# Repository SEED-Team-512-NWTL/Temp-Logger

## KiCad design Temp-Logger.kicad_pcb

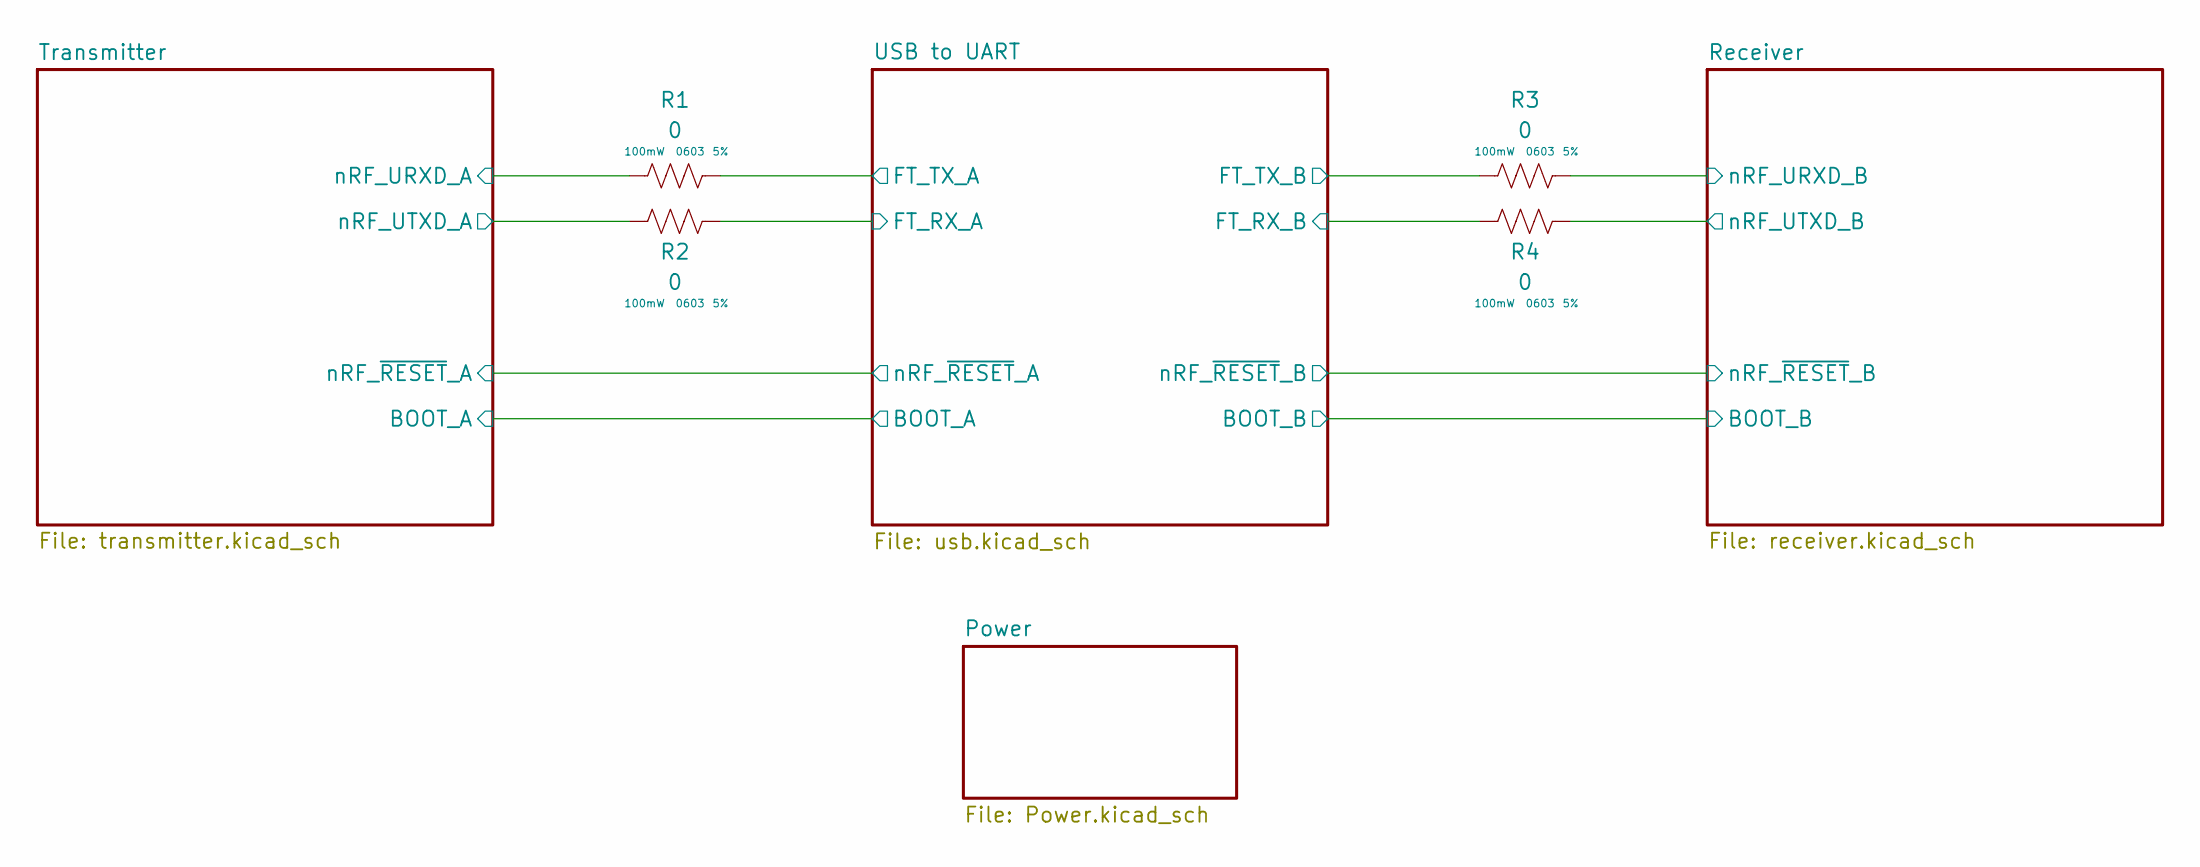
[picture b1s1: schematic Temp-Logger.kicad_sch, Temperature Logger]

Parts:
R1, R2, R3, R4: 0; R_0603_1608Metric_Pad0.98x0.95mm_HandSolder; Tolerance 5%; LCSC C177335

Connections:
/Receiver/nRF_URXD_B: R3.2; also elsewhere on the board
/Receiver/nRF_UTXD_B: R4.2; also elsewhere on the board
/Transmitter/nRF_URXD_A: R1.1; also elsewhere on the board
/Transmitter/nRF_UTXD_A: R2.1; also elsewhere on the board
/USB to UART/FT_RX_A: R2.2; also elsewhere on the board
/USB to UART/FT_RX_B: R4.1; also elsewhere on the board
/USB to UART/FT_TX_A: R1.2; also elsewhere on the board
/USB to UART/FT_TX_B: R3.1; also elsewhere on the board

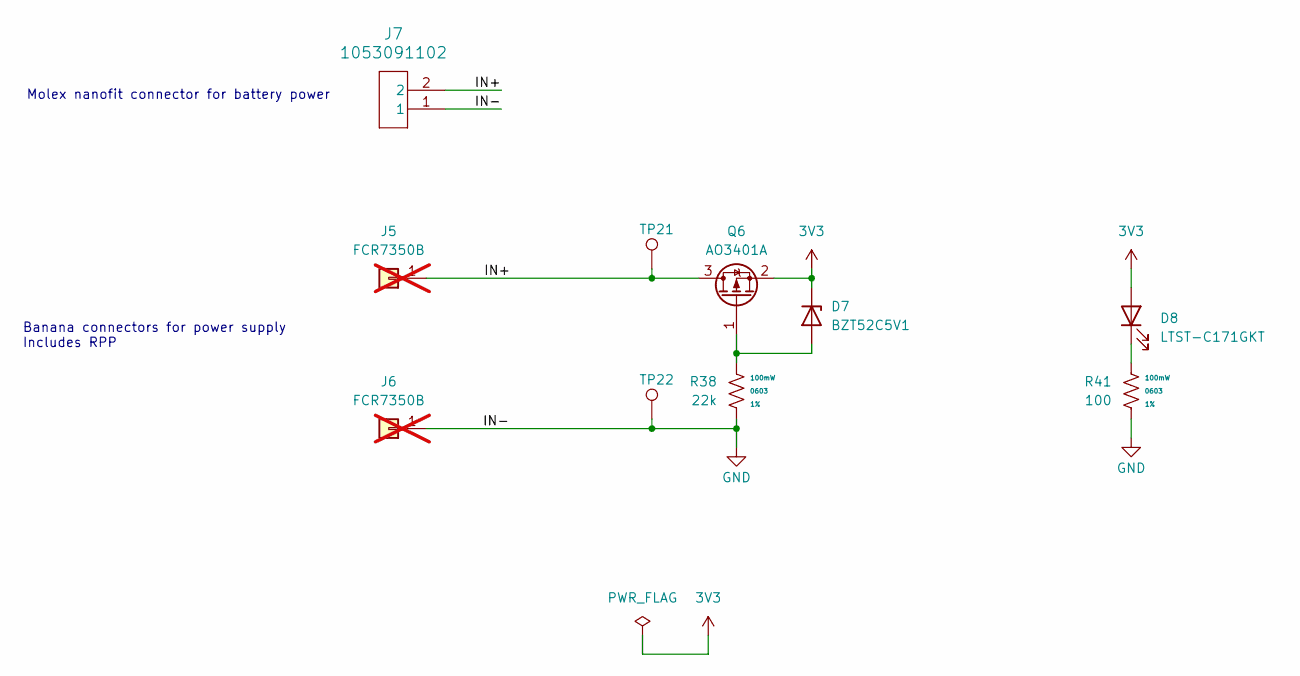
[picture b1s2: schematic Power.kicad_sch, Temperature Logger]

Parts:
D7: BZT52C5V1; D_SOD-123; LCSC C2117
D8: LTST-C171GKT; LED_0805_2012Metric; LCSC C913075
J5, J6: FCR7350B; Banana_Cliff_FCR7350B_S16N-PC_Horizontal; not fitted
J7: 1053091102; LCSC C2938824
Q6: AO3401A; SOT-23; LCSC C15127
R38: 22k; R_0603_1608Metric_Pad0.98x0.95mm_HandSolder; Tolerance 1%; LCSC C114065
R41: 100; R_0603_1608Metric_Pad0.98x0.95mm_HandSolder; Tolerance 1%; LCSC C105588
TP21, TP22: 1.0mm; TestPoint_Pad_D1.0mm

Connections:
3V3: D7.1 (K), D8.2 (A), Q6.2 (S); also elsewhere on the board
/Power/IN+: J5.1 (Pin_1_1), J7.2, Q6.3 (D), TP21.1 (1_1)
GND: J6.1 (Pin_1_1), J7.1, R38.1, R41.1, TP22.1 (1_1); also elsewhere on the board
unnamed: D7.2 (A), Q6.1 (G), R38.2
unnamed: D8.1 (K), R41.2

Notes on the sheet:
Banana connectors for power supply Includes RPP
Molex nanofit connector for battery power

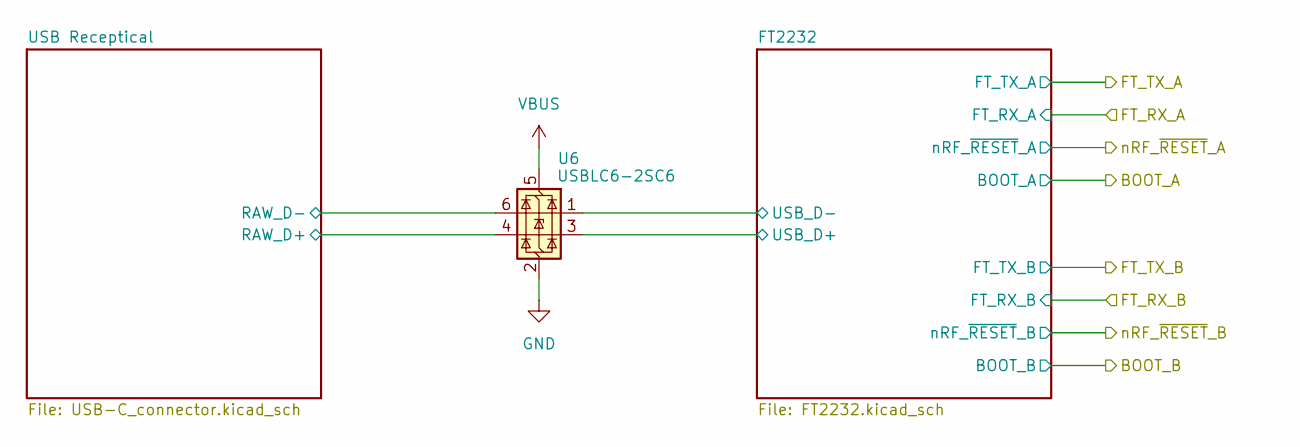
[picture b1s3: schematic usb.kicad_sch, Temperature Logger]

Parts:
U6: USBLC6-2SC6; SOT-23-6; LCSC C7519

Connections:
/USB to UART/FT2232/USB_D+: U6.3 (I/O2); also elsewhere on the board
/USB to UART/FT2232/USB_D-: U6.1 (I/O1); also elsewhere on the board
/USB to UART/USB Receptical/RAW_D+: U6.4 (I/O2); also elsewhere on the board
/USB to UART/USB Receptical/RAW_D-: U6.6 (I/O1); also elsewhere on the board
GND: U6.2 (GND); also elsewhere on the board
VBUS: U6.5 (VBUS); also elsewhere on the board

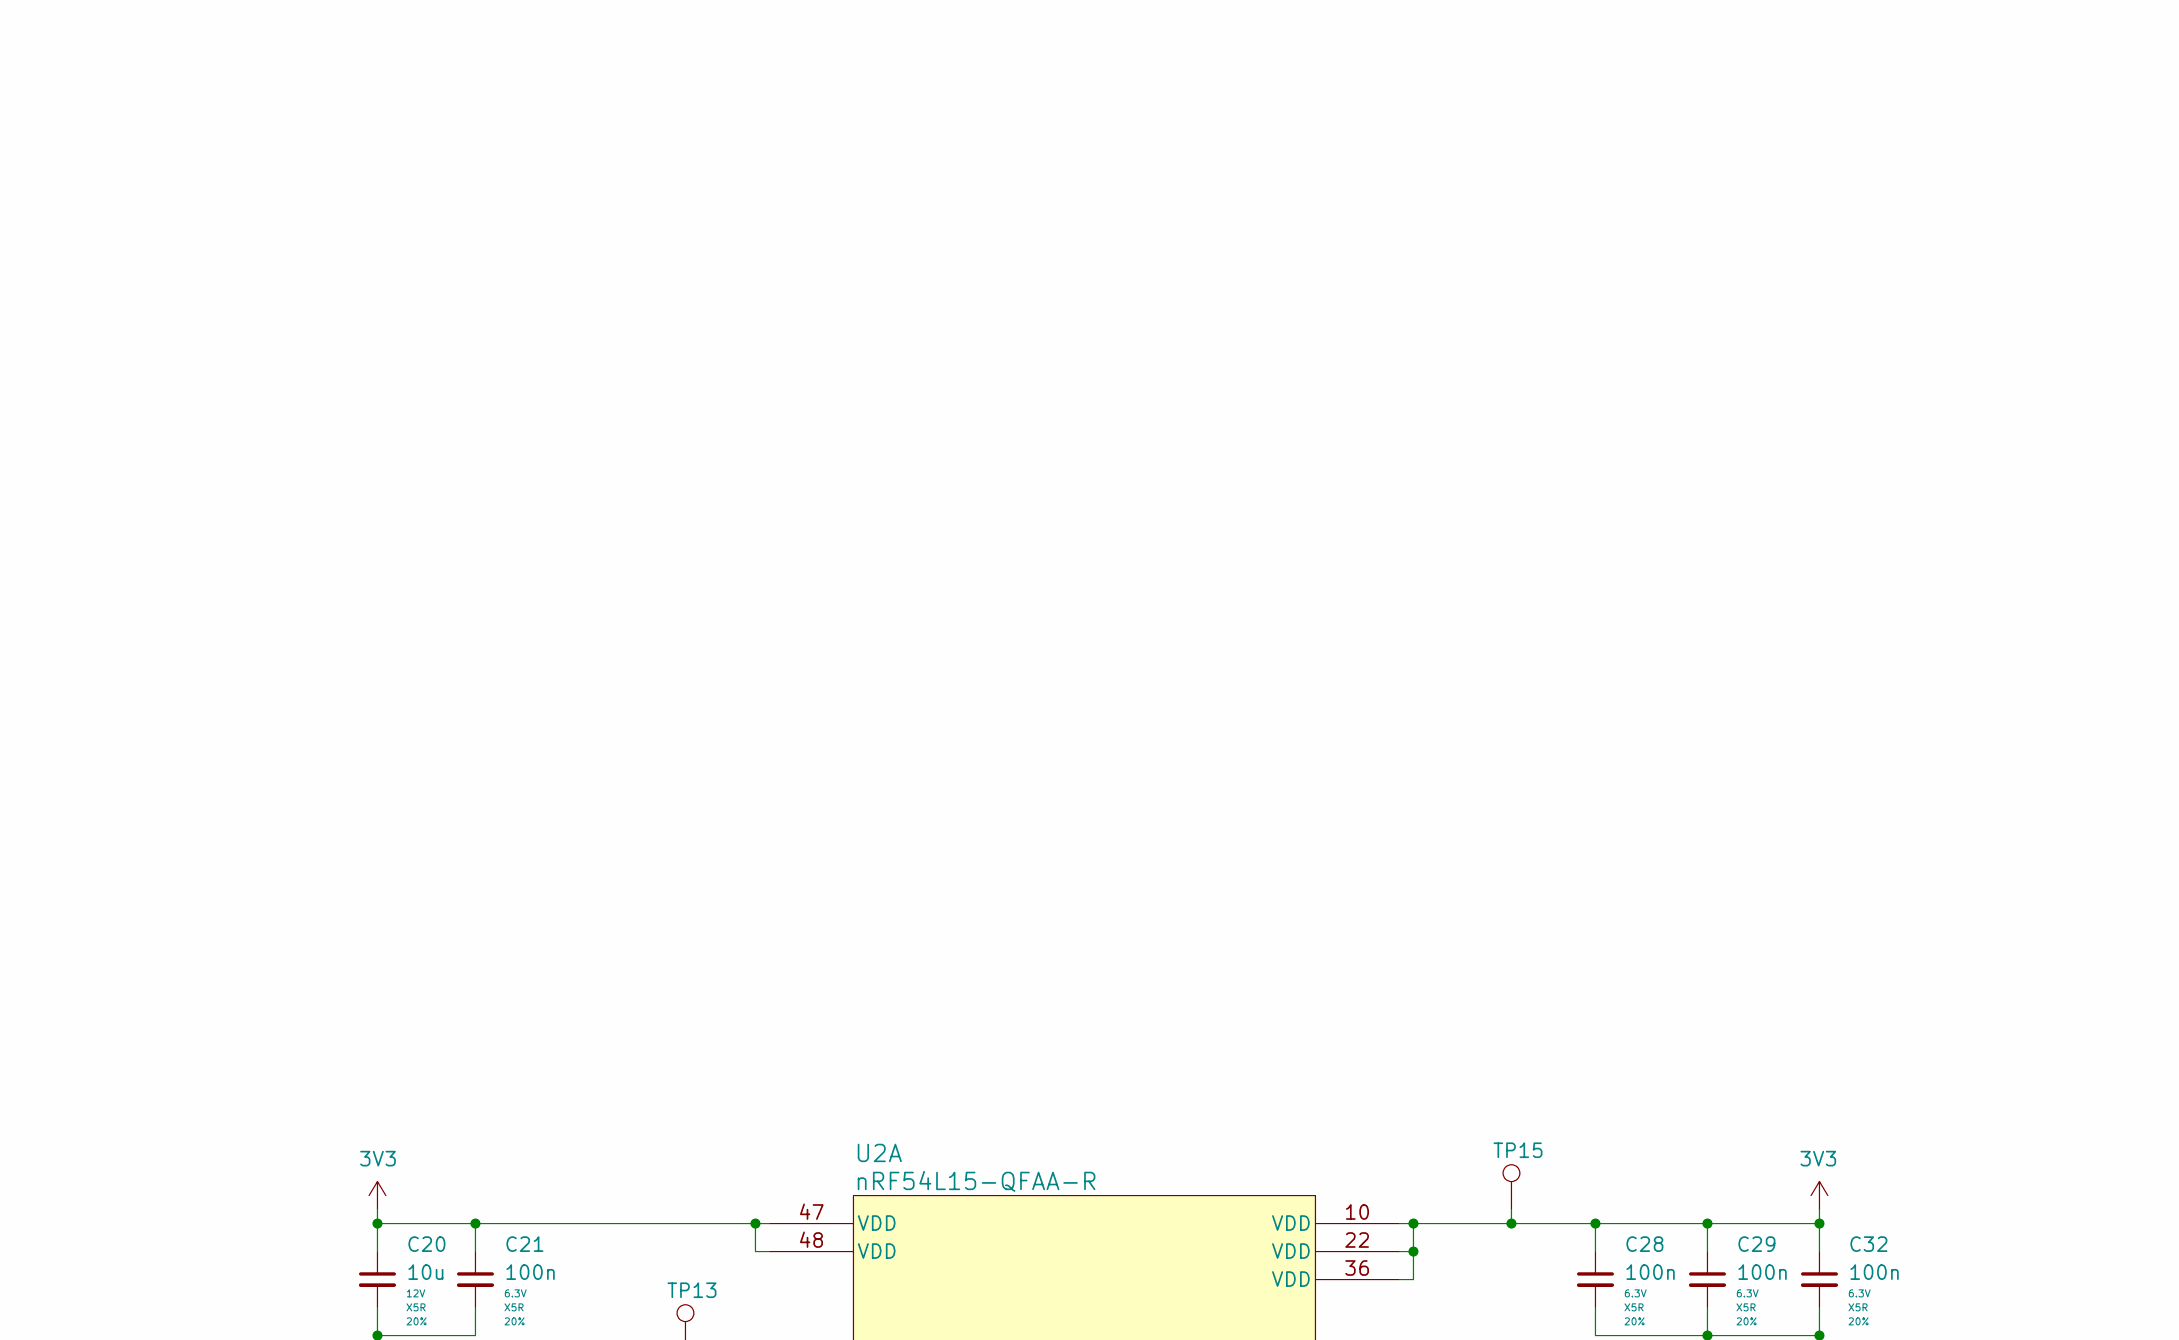
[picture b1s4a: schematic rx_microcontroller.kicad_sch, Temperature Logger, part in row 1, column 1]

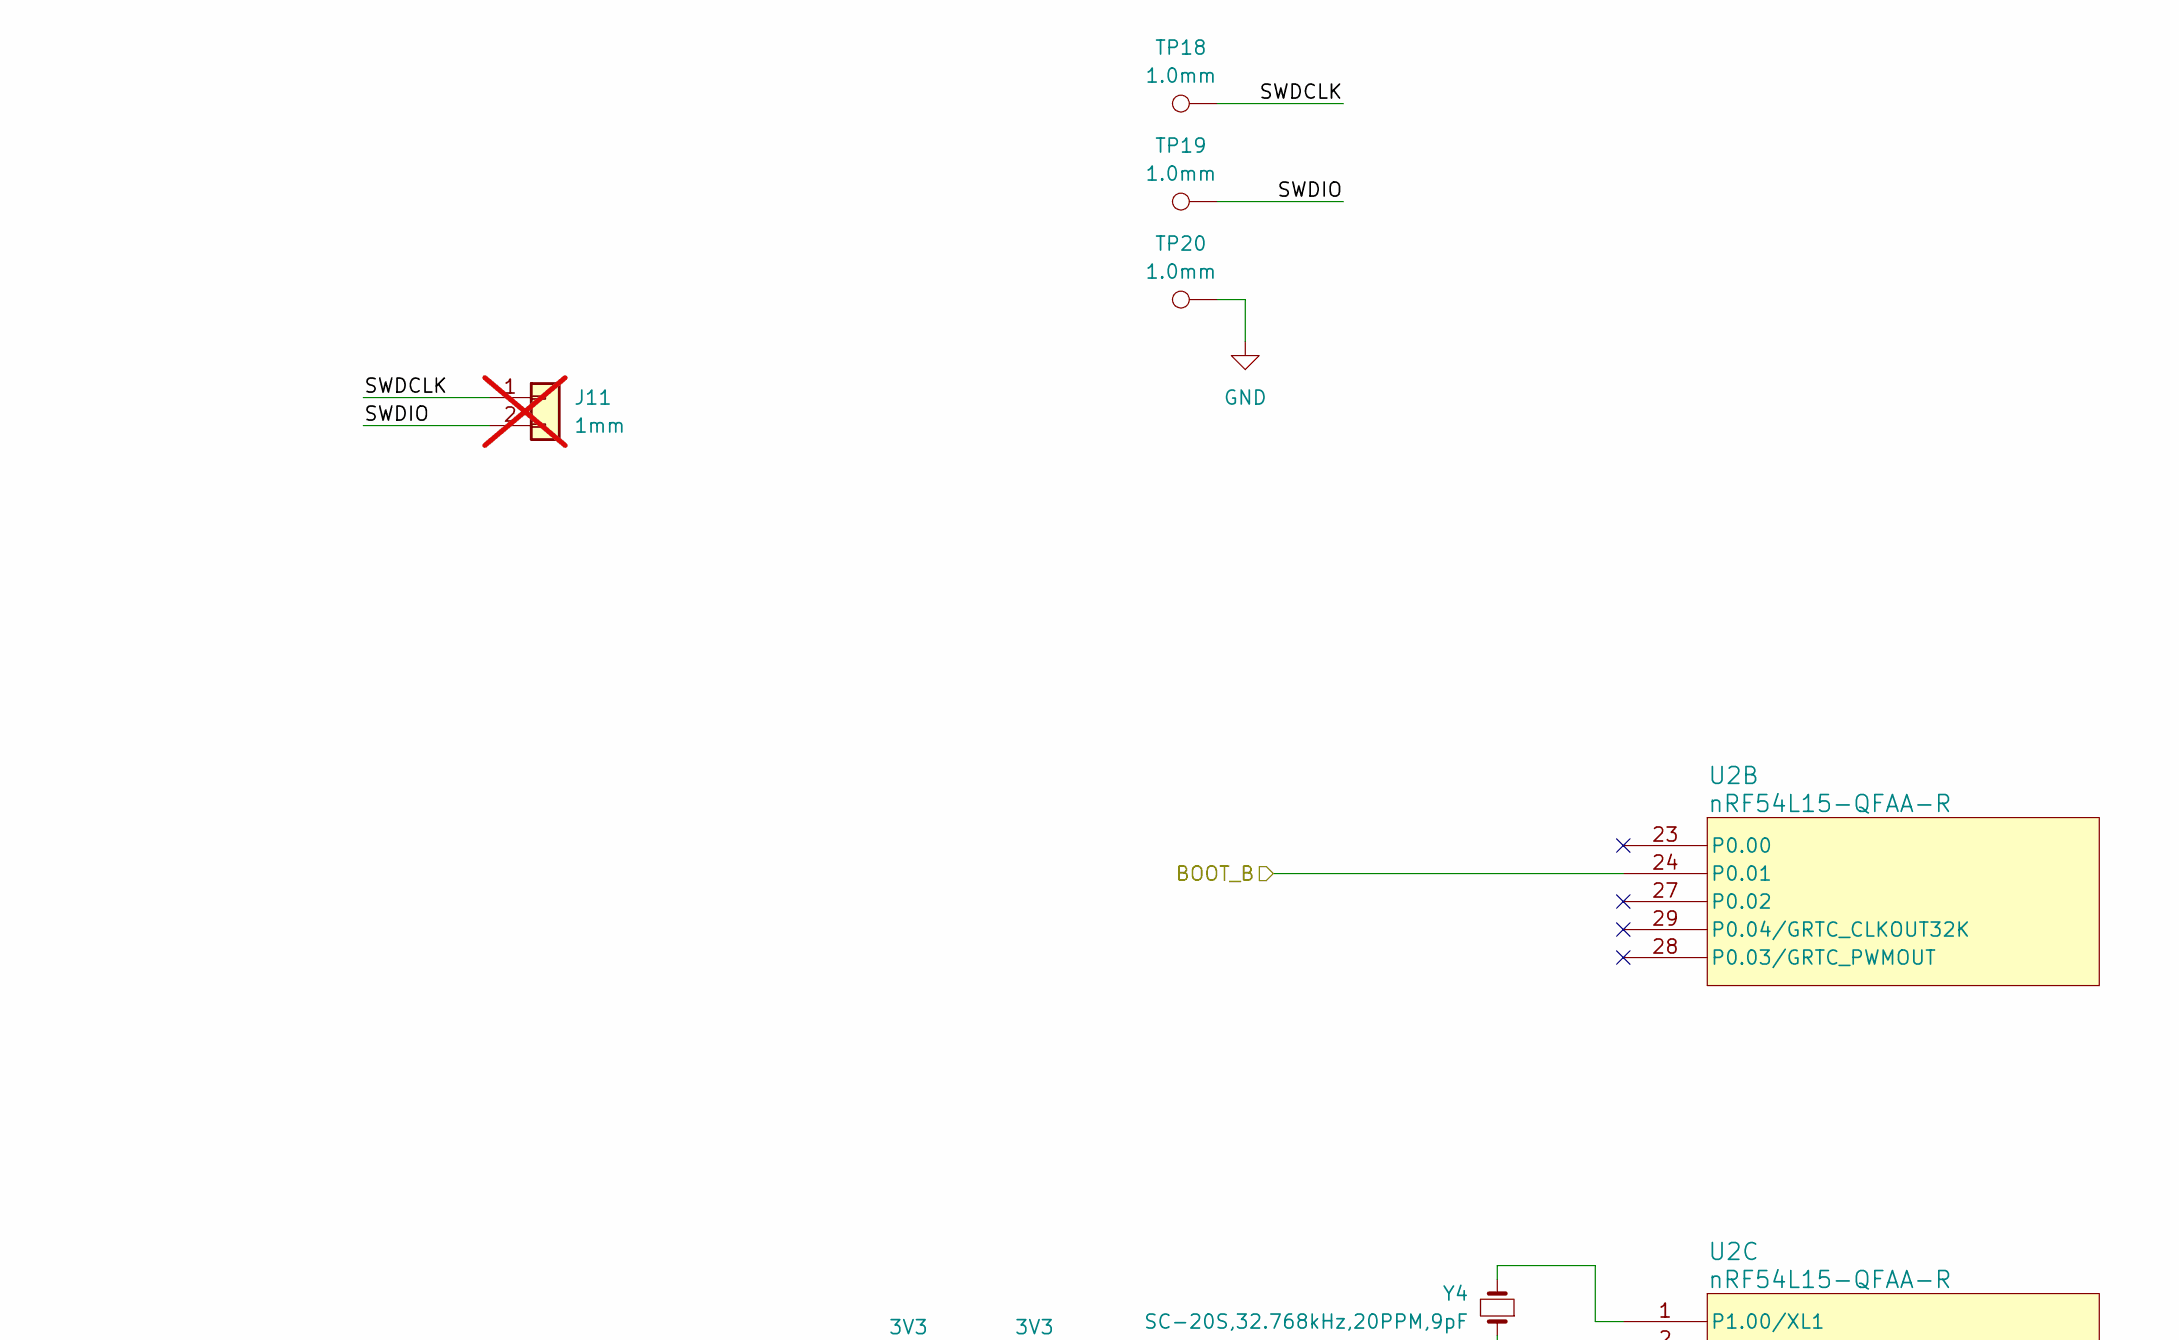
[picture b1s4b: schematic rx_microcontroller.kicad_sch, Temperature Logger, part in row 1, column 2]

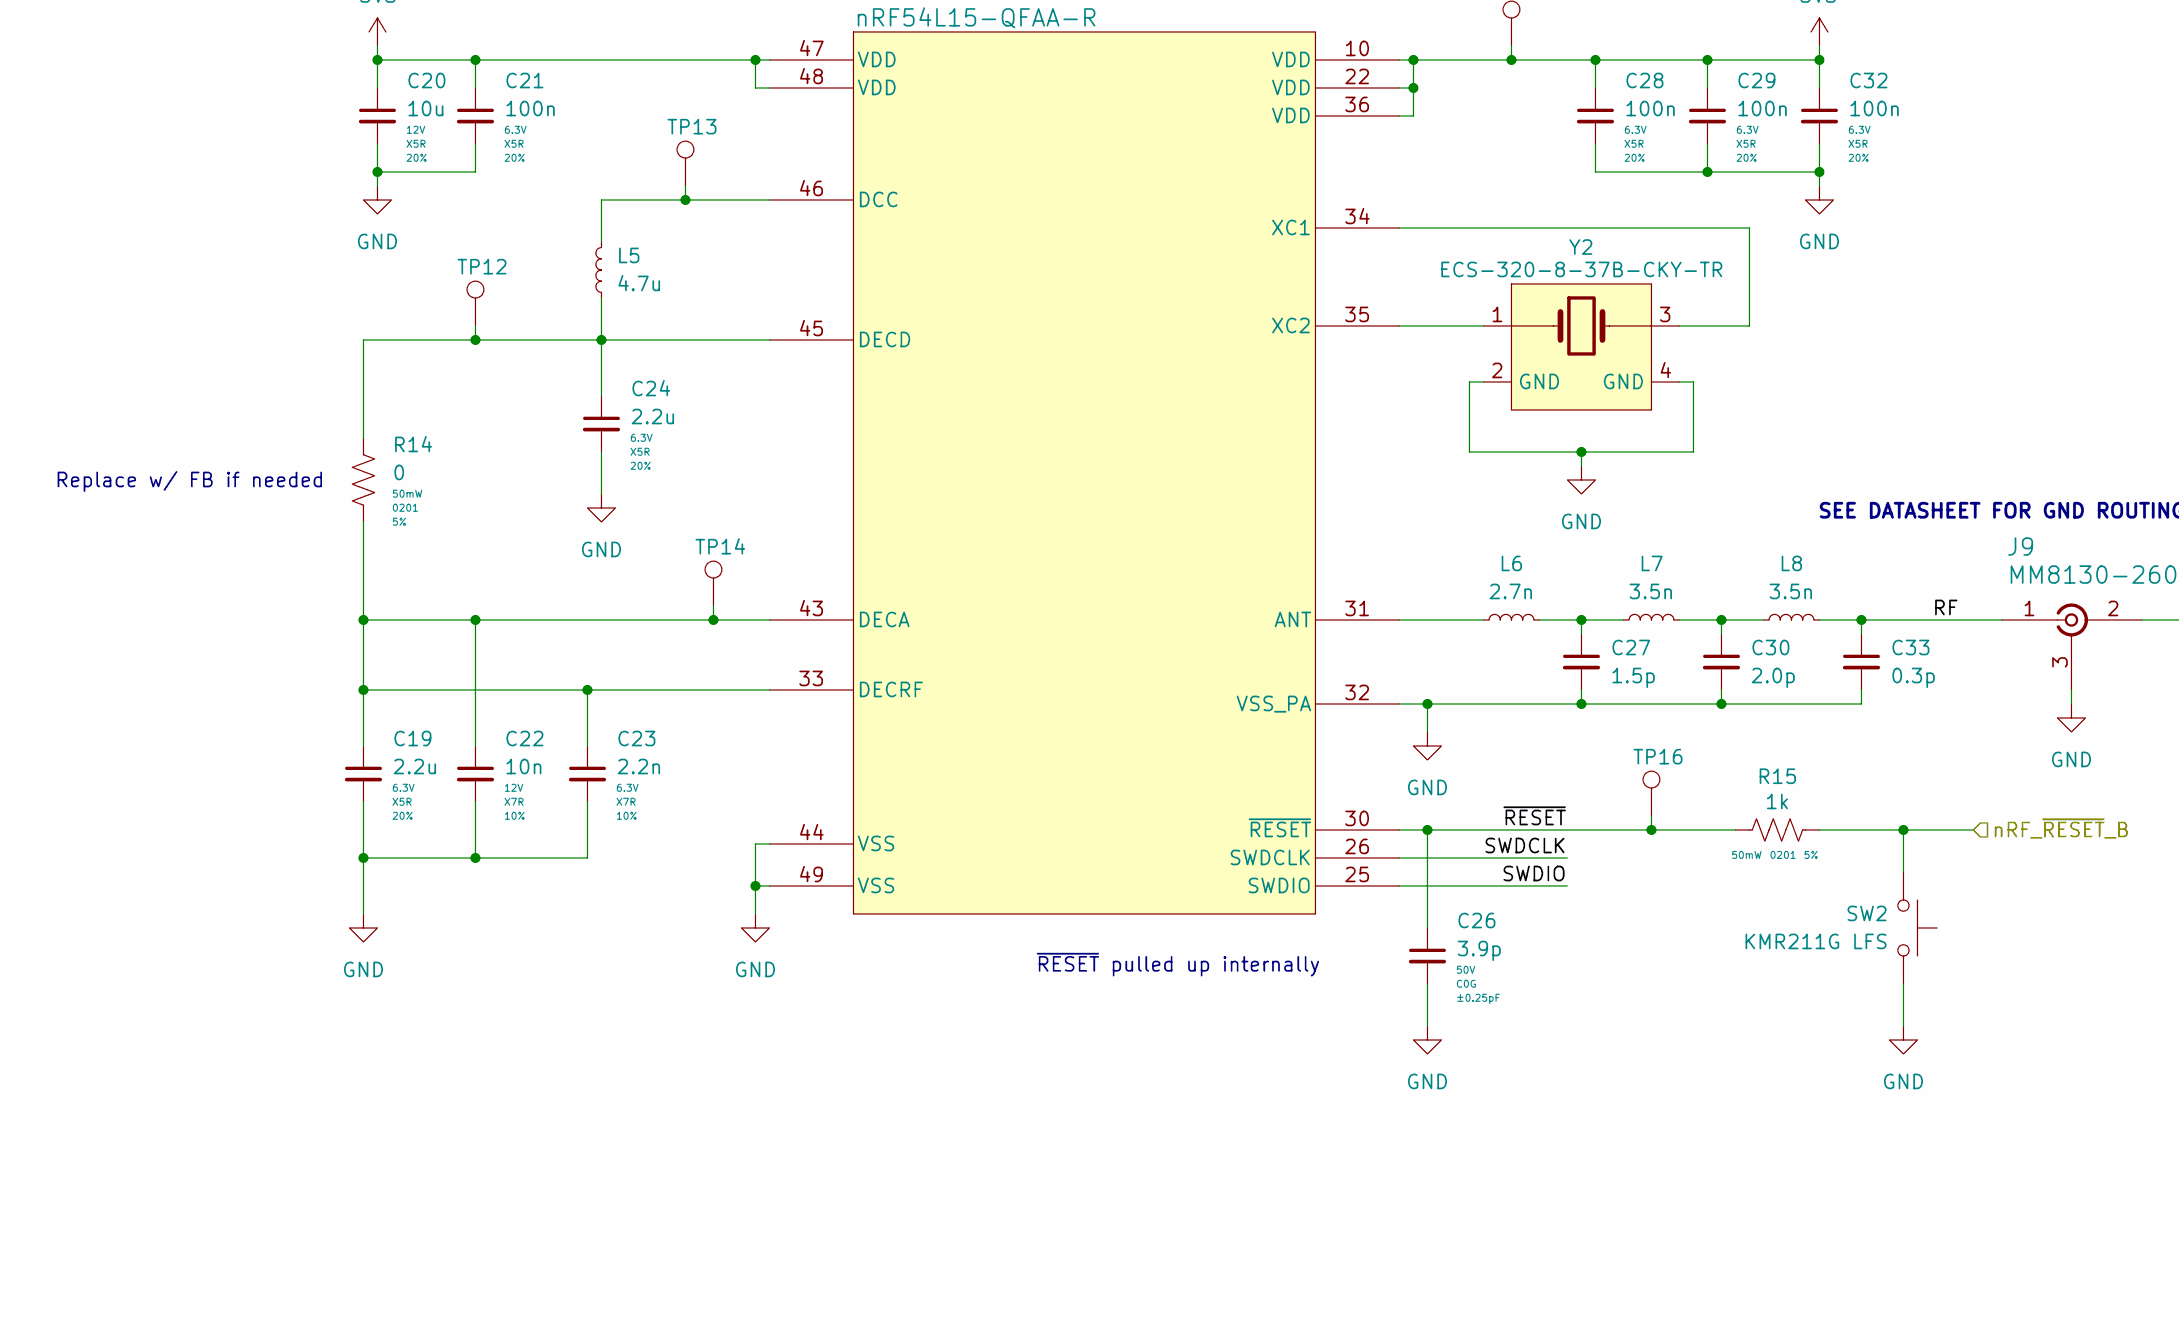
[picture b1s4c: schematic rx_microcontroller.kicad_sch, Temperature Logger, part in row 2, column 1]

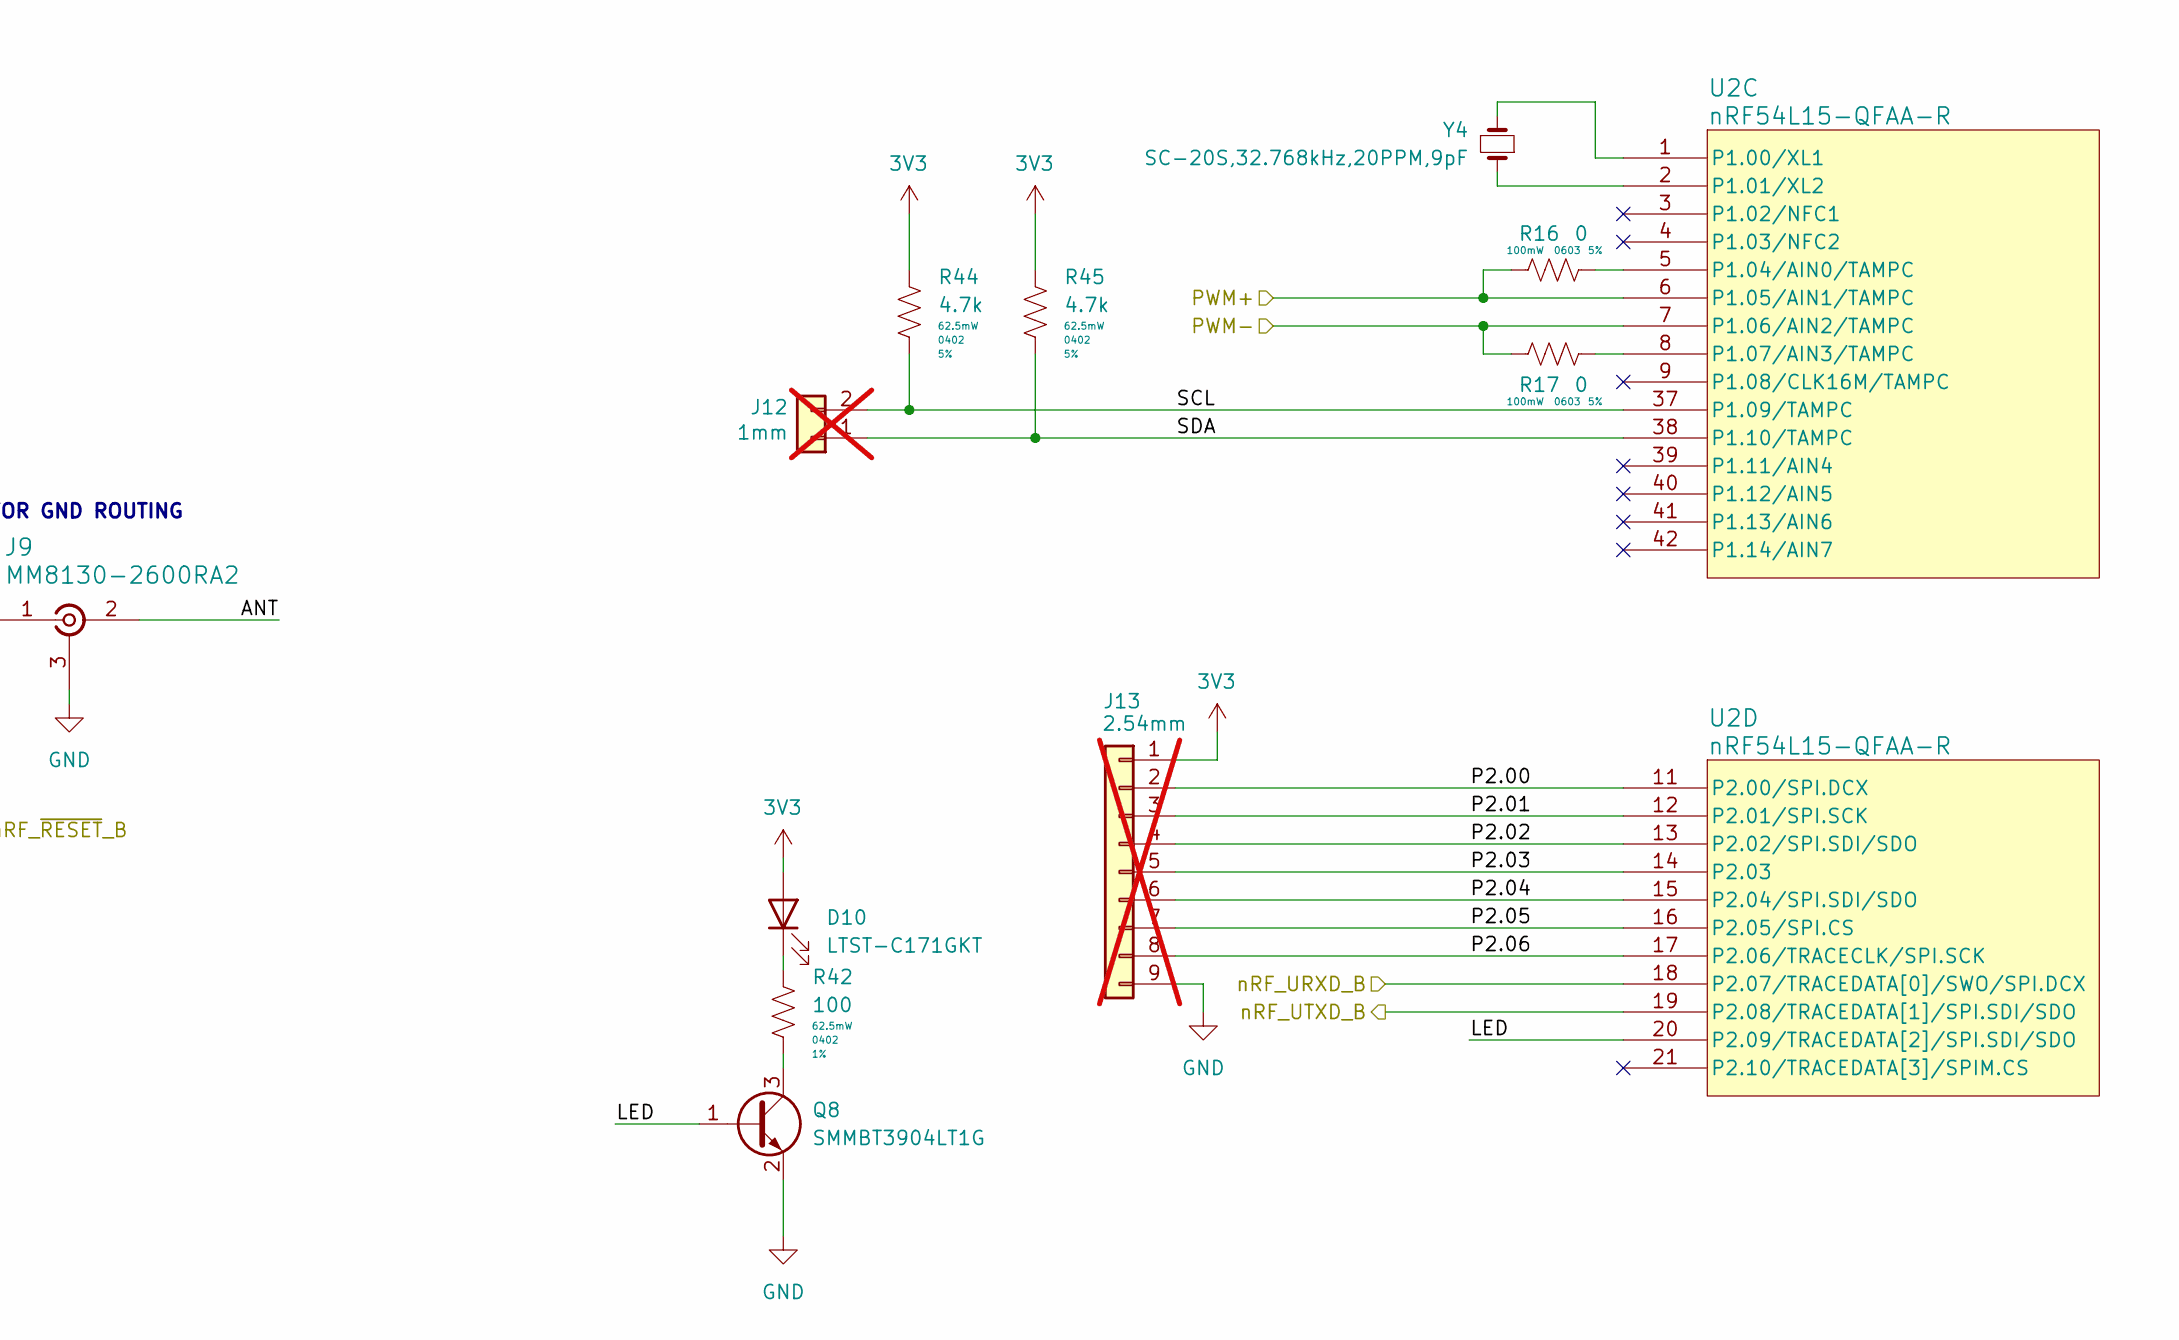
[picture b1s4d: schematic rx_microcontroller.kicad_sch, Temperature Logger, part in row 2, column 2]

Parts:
C19, C24: 2.2u; C_0201_0603Metric; Voltage Rating 6.3V; Tolerance 20%; LCSC C76933
C20: 10u; C_0402_1005Metric_Pad0.74x0.62mm_HandSolder; Voltage Rating 12V; Tolerance 20%; LCSC C15525
C21, C28, C29, C32: 100n; C_0201_0603Metric; Voltage Rating 6.3V; Tolerance 20%; LCSC C284992
C22: 10n; C_0201_0603Metric; Voltage Rating 12V; Tolerance 10%; LCSC C309453
C23: 2.2n; C_0201_0603Metric; Voltage Rating 6.3V; Tolerance 10%; LCSC C526947
C26: 3.9p; C_0201_0603Metric; Voltage Rating 50V; Tolerance ±0.25pF; LCSC C76926
C27: 1.5p; C_0201_0603Metric; Part Number GJM0335C1E1R5WB01; LCSC C435397
C30: 2.0p; C_0201_0603Metric; Part Number GJM0335C1E2R0WB01; LCSC C668326
C33: 0.3p; C_0201_0603Metric; LCSC C76927
D10: LTST-C171GKT; LED_0805_2012Metric; LCSC C913075
J9: MM8130-2600RA2; LCSC C167503
J11, J12: 1mm; PinHeader_1x02_P1.00mm_Vertical; not fitted
J13: 2.54mm; PinHeader_1x09_P2.54mm_Vertical; not fitted
L5: 4.7u; L_0603_1608Metric; LCSC C76799
L6: 2.7n; L_0201_0603Metric; Part Number GJM0335C1E1R5WB01; LCSC C7216765
L7, L8: 3.5n; L_0201_0603Metric; Part Number LQP03HQ3N5B02; LCSC C3911055
Q8: SMMBT3904LT1G; LCSC C84555
R14: 0; R_0201_0603Metric; Tolerance 5%; LCSC C100147
R15: 1k; R_0201_0603Metric; Tolerance 5%; LCSC C131396
R16, R17: 0; R_0603_1608Metric_Pad0.98x0.95mm_HandSolder; Tolerance 5%; LCSC C177335
R42: 100; R_0402_1005Metric_Pad0.72x0.64mm_HandSolder; Tolerance 1%; LCSC C82865
R44, R45: 4.7k; R_0402_1005Metric_Pad0.72x0.64mm_HandSolder; Tolerance 5%; LCSC C105870
SW2: KMR211G LFS; SW_Push_1P1T_NO_CK_KMR2; LCSC C221675
TP12, TP13, TP14, TP15, TP16, TP18, TP19, TP20: 1.0mm; TestPoint_Pad_D1.0mm
U2: nRF54L15-QFAA-R; NRF54L15-QFAA-R
Y2: ECS-320-8-37B-CKY-TR; LCSC C2636238
Y4: SC-20S,32.768kHz,20PPM,9pF; LCSC C97603

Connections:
3V3: C20.1, C21.1, C28.1, C29.1, C32.1, D10.2 (A), J13.1, R44.1, R45.1, TP15.1 (1_1), U2.10 (VDD), U2.22 (VDD), U2.36 (VDD), U2.47 (VDD), U2.48 (VDD); also elsewhere on the board
/Receiver/BOOT_B: U2.24 (P0.01); also elsewhere on the board
/Receiver/Piezoelectric/PWM+: R16.1, U2.6 (P1.05/AIN1/TAMPC); also elsewhere on the board
/Receiver/Piezoelectric/PWM-: R17.1, U2.7 (P1.06/AIN2/TAMPC); also elsewhere on the board
/Receiver/RX Microcontroller/ANT: J9.2 (OUT)
/Receiver/RX Microcontroller/LED: Q8.1 (B), U2.20 (P2.09/TRACEDATA[2]/SPI.SDI/SDO)
/Receiver/RX Microcontroller/P2.00: J13.2, U2.11 (P2.00/SPI.DCX)
/Receiver/RX Microcontroller/P2.01: J13.3, U2.12 (P2.01/SPI.SCK)
/Receiver/RX Microcontroller/P2.02: J13.4, U2.13 (P2.02/SPI.SDI/SDO)
/Receiver/RX Microcontroller/P2.03: J13.5, U2.14 (P2.03)
/Receiver/RX Microcontroller/P2.04: J13.6, U2.15 (P2.04/SPI.SDI/SDO)
/Receiver/RX Microcontroller/P2.05: J13.7, U2.16 (P2.05/SPI.CS)
/Receiver/RX Microcontroller/P2.06: J13.8, U2.17 (P2.06/TRACECLK/SPI.SCK)
/Receiver/RX Microcontroller/RF: C33.1, J9.1 (IN), L8.2
/Receiver/RX Microcontroller/SCL: J12.2, R44.2, U2.37 (P1.09/TAMPC)
/Receiver/RX Microcontroller/SDA: J12.1, R45.2, U2.38 (P1.10/TAMPC)
/Receiver/RX Microcontroller/SWDCLK: J11.1, TP18.1 (1_1), U2.26 (SWDCLK)
/Receiver/RX Microcontroller/SWDIO: J11.2, TP19.1 (1_1), U2.25 (SWDIO)
/Receiver/RX Microcontroller/~RESET: C26.1, R15.1, TP16.1 (1_1), U2.30 (~RESET)
/Receiver/nRF_URXD_B: U2.18 (P2.07/TRACEDATA[0]/SWO/SPI.DCX); also elsewhere on the board
/Receiver/nRF_UTXD_B: U2.19 (P2.08/TRACEDATA[1]/SPI.SDI/SDO); also elsewhere on the board
/Receiver/nRF_~RESET_B: R15.2, SW2.2; also elsewhere on the board
GND: C19.2, C20.2, C21.2, C22.2, C23.2, C24.2, C26.2, C27.2, C28.2, C29.2, C30.2, C32.2, C33.2, J9.3 (GND), J9.4 (GND), J9.5 (GND), J9.6 (GND), J13.9, Q8.2 (E), SW2.1, TP20.1 (1_1), U2.32 (VSS_PA), U2.44 (VSS), U2.49 (VSS), Y2.2 (GND), Y2.4 (GND); also elsewhere on the board
unnamed: C27.1, L6.2, L7.1
unnamed: C30.1, L7.2, L8.1
unnamed: D10.1 (K), R42.1
unnamed: Q8.3 (C), R42.2
unnamed: L6.1, U2.31 (ANT)
unnamed: L5.2, TP13.1 (1_1), U2.46 (DCC)
unnamed: C19.1, C22.1, C23.1, R14.1, TP14.1 (1_1), U2.33 (DECRF), U2.43 (DECA)
unnamed: C24.1, L5.1, R14.2, TP12.1 (1_1), U2.45 (DECD)
unnamed: U2.34 (XC1), Y2.3
unnamed: U2.35 (XC2), Y2.1
unnamed: U2.1 (P1.00/XL1), Y4.2
unnamed: U2.2 (P1.01/XL2), Y4.1
unnamed: R16.2, U2.5 (P1.04/AIN0/TAMPC)
unnamed: R17.2, U2.8 (P1.07/AIN3/TAMPC)

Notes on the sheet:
~{RESET} pulled up internally
Replace w/ FB if needed
SEE DATASHEET FOR GND ROUTING

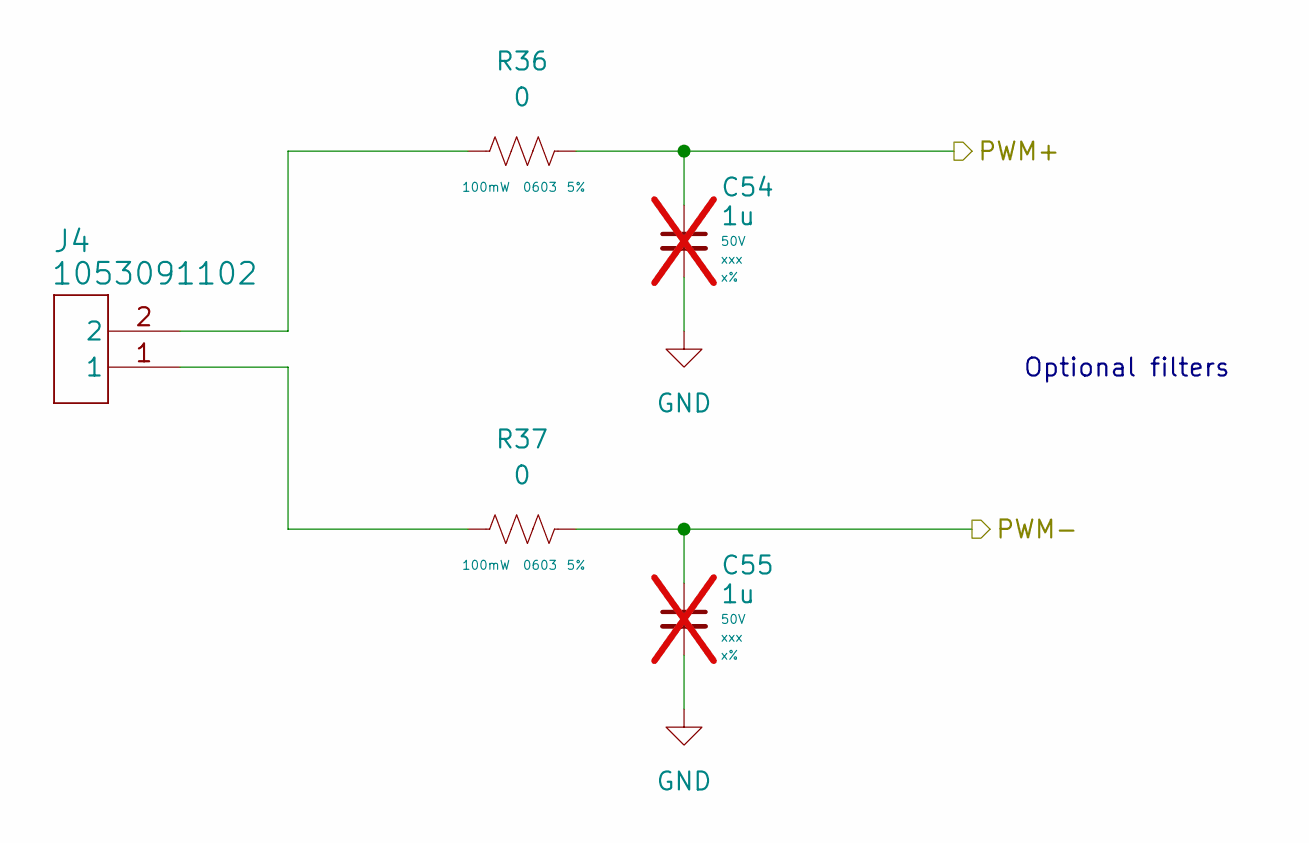
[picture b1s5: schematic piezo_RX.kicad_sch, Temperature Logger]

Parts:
C54, C55: 1u; C_0603_1608Metric_Pad1.08x0.95mm_HandSolder; Voltage Rating 50V; Tolerance x%; not fitted
J4: 1053091102; LCSC C2938824
R36, R37: 0; R_0603_1608Metric_Pad0.98x0.95mm_HandSolder; Tolerance 5%; LCSC C177335

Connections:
/Receiver/Piezoelectric/PWM+: C54.1, R36.2; also elsewhere on the board
/Receiver/Piezoelectric/PWM-: C55.1, R37.2; also elsewhere on the board
GND: C54.2, C55.2; also elsewhere on the board
unnamed: J4.1, R37.1
unnamed: J4.2, R36.1

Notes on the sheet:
Optional filters
